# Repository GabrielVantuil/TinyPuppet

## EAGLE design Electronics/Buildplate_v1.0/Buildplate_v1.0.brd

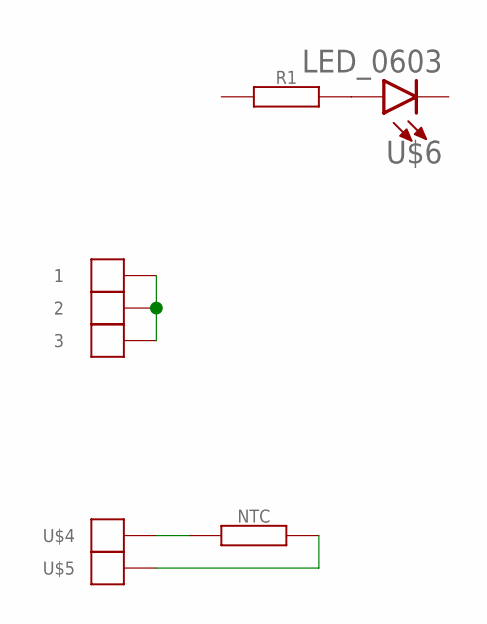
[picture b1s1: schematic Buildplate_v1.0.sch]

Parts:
1, 2, 3: PAD_POGOPIN_1.3MM
NTC: RESISTOR0603-RES; 0603-RES
R1: RESISTOR0603-RES; 0603-RES
U$4, U$5: PAD_50X100MIL
U$6: LED_0603; 0603

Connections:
unnamed: R1.2, U$6.A
unnamed: NTC.1, U$4.P$1
unnamed: NTC.2, U$5.P$1
unnamed: 1.P$1, 2.P$1, 3.P$1

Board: 2 copper layers, 8 parts (0 on the bottom side), 4 nets, no tracks yet.

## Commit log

2025-05-26 First sketch, string coreXY, 120x120x120 print volume, 200x200x300 total volume
2025-07-03 Functional version, lots of changes
2025-07-03 Marlin firmware working
2025-07-11 Electronics
2025-07-20 Changed power supply and adding electronics panels
2025-10-26 120x120mm heated bed
